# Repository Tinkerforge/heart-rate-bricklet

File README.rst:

Heart Rate Bricklet
===================

**The development of this Bricklet was stopped.**

This repository contains the firmware source code and the hardware design
files. The documentation generator configs can be found at
https://github.com/Tinkerforge/generators

Repository Content
------------------

software/:
 * examples/: Examples for all supported languages
 * build/: Compiled files
 * src/: Source code of firmware
 * Makefile: Makefile to build project

hardware/:
 * Contains KiCad project files and additionally schematics as PDF

datasheets/:
 * Contains datasheets for sensors and complex ICs that are used

Hardware
--------

The hardware is designed with the open source EDA Suite KiCad
(http://www.kicad.org). Before you are able to open the files,
you have to install the Tinkerforge kicad-libraries
(https://github.com/Tinkerforge/kicad-libraries). You can either clone
them directly in hardware/ or clone them in a separate folder and
symlink them into hardware/
(ln -s kicad_path/kicad-libraries project_path/hardware). After that you
can open the .pro file in hardware/ with KiCad and from there view and
modify the schematics and the PCB layout.

Software
--------

If you want to do your own Brick/Bricklet firmware development we highly
recommend that you use our build environment setup script and read the
tutorial (https://www.tinkerforge.com/en/doc/Tutorials/Tutorial_Build_Environment/Tutorial.html).

To compile the C code we recommend you to install the newest GNU Arm Embedded
Toolchain (https://launchpad.net/gcc-arm-embedded/+download).
You also need to install bricklib (https://github.com/Tinkerforge/bricklib)
and brickletlib (https://github.com/Tinkerforge/brickletlib).

You can either clone it directly in software/src/ or clone it in a
separate folder and symlink it into software/src/
(ln -s bricklib_path/bricklib project_path/software/src/ and
ln -s brickletlib_path/brickletlib project_path/software/src/).
Finally make sure to have CMake installed
(http://www.cmake.org/cmake/resources/software.html).

After that you can build the firmware by invoking make in software/.
The firmware (.bin) can then be found in software/build/ and uploaded
with brickv (click button "Flashing" on start screen).

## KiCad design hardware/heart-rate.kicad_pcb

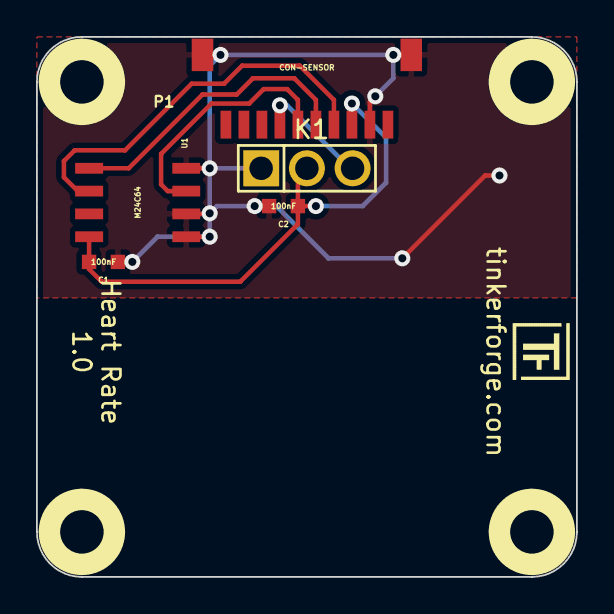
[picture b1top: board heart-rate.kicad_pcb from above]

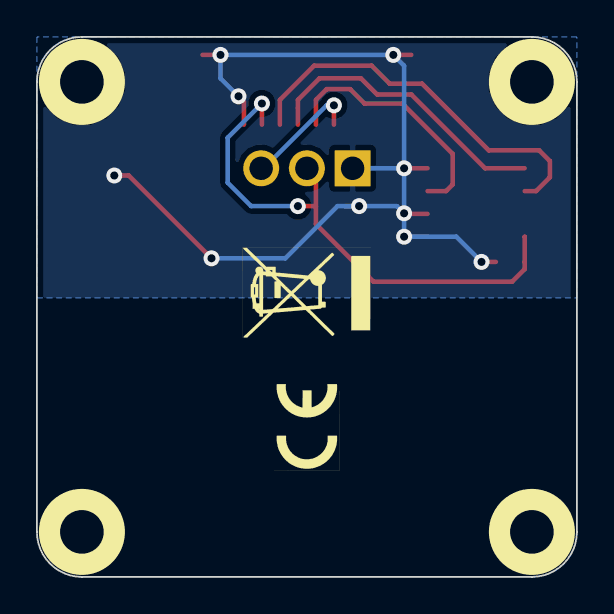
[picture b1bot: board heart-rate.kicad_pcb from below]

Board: 2 copper layers, 30.0 x 30.0 mm, 11 parts (2 on the bottom side), 6 nets.

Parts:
C1, C2: 100nF; 0603
K1: CONN_3; PIN_ARRAY_3X1
P1: CON-SENSOR
U1: M24C64; SOIC8
U2, U3, U4, U5: DRILL; DRILL_NP
VAL: CE_5mm
VAL#2: WEEE_7mm

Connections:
GND: C1.1, C2.2, K1.1, P1.2, P1.EP, U1.1, U1.2, U1.4
unnamed: K1.3, P1.7
unnamed: P1.6, U1.3
SCL: P1.4, U1.6
SDA: P1.5, U1.5
VCC: C1.2, C2.1, K1.2, P1.3, U1.8

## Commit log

2014-03-13 heart-rate-bricklet: adding firmware source
2014-03-13 heart-rate-bricklet: adding perl examples
2014-03-13 heart-rate-bricklet: adding php exmaples
2014-03-13 heart-rate-bricklet: adding java examples
2014-03-13 heart-rate-bricklet: adding C examples
2014-03-13 heart-rate-bricklet: adding javascript examples
2014-03-13 heart-rate-bricklet: adding csharp exmaples
2014-03-13 heart-rate-bricklet: adding VB.NET examples
2014-03-13 heart-rate-bricklet: adding ruby examples
2014-03-13 heart-rate-bricklet: adding delphi examples
2014-03-13 heart-rate-bricklet: adding shell examples
2014-03-19 heart rate sensor bricklet hardware files
2014-04-02 java: Unify constants style
2014-04-02 perl: Unify print style
2014-04-16 new errata
2014-07-15 java: Replace System.console() usage with an Eclipse compatible pattern
2014-08-06 Some whitespace and string cleanup
2015-02-13 csharp,vbnet: Use ReadLine instead of ReadKey
    Because ReadKey doesn't work with a pipe as stdin on the RED Brick.
2015-02-13 csharp: Use ReadLine instead of ReadKey
    Because ReadKey doesn't work with a pipe as stdin on the RED Brick.
2015-03-02 windows: Stop cmake from searching for mingw32-make.exe
    Using MinGW Makefiles as generator makes cmake search for mingw32-make.exe
    which might not be installed because GnuWin32's make.exe is used instead.
2015-04-09 c: Whitespace
2015-06-18 Break long lines in JavaScript examples
    Remove JavaScript bindings.
2015-06-24 javascript: Clean up output creation
2015-06-24 java: Remove unnecessary parentheses
2015-06-24 Fix typos in examples
2015-06-24 vbnet: Use correct type
2015-07-23 Make JavaScript browser example textarea readonly
2015-07-25 Remove double readonly
2015-07-27 Cleanup C/C++, C#, Java, Python and Ruby examples
2015-07-29 Reformat changelog
2015-08-07 Use full device class name in Python examples
2015-08-12 Fix minor warnings in C/C++ examples
2015-08-14 Cleanup Delphi examples
2015-08-18 Cleanup VB.NET examples
2015-08-19 Cleanup Perl examples
2015-08-21 Use shorter print statement in Perl example
2015-09-10 Duplicate cmake call to fix bug during cmake creation
2015-09-24 Add Mathematica and MATLAB/Octave examples
2015-09-30 Generator based example cleanup
2015-11-12 matlab: Fix callback handling for R2014a
    http://undocumentedmatlab.com/blog/matlab-callbacks-for-java-events-in-r2014a
2015-11-25 Include date and commit into changelog
2016-05-18 c: Add missing device destroy call
2016-07-01 Make the change UID comment more explicit
2017-04-13 csharp: Adapt example
2017-06-02 octave: Use javaObject instead of deprecated java_new
2017-11-30 Update examples from generator
2017-12-07 mathematica: Also generate .nb files
2018-01-26 c: Fine-tune printf format
2018-02-02 Update examples
2018-02-19 javascript: Close div tag correctly
2018-02-20 Cleanup KiCad libraries config
    Ensure LibDir=kicad-libraries and LibName1=tinkerforge.
    Remove special library.
2018-05-24 perl: Use strict in examples
2018-06-28 Fix readme
2018-07-13 Add Makefile with docker support
2018-07-13 Update directory structure and build instructions
2018-07-13 Remove obsolete generate_makefile scripts
2018-09-14 vbnet: Fix typo in comment
2018-11-06 Add rust examples
2018-11-07 rust: Accept host names for ip connection, fix naming inconsistencies
2018-11-07 rust: Rename callback receivers.
2018-12-14 Add go examples.
2018-12-18 go: Change import path.
2018-12-18 go: Change import path again.
2018-12-20 rust: Reformat examples.
2019-01-24 mqtt: Add examples.
2019-01-24 mqtt: Fix example header.
2019-01-24 mqtt: Remove executable bit in example permissions.
2019-01-24 go: Minor example fixes.
2019-01-24 mqtt: Minor example fixes.
2019-03-28 mqtt: Fix whitespace.
2019-08-22 c: Adapt to bindings changes
2019-12-02 Remove examples
2019-12-02 Mark development as stopped
2020-01-13 examples: mqtt: Remove trailing whitespace.
2021-10-25 Update KiCad link
    https://www.kicad.org/blog/2021/10/Avoid-links-to-former-kicad-domain/
2022-07-06 Add license files.

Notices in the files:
hardware/heart-rate.kicad_pcb:
Licensed under CERN OHL v.1.1
Copyright (©) 2014, B.Nordmeyer
Copyright Tinkerforge GmbH 2014.
This documentation describes Open Hardware and is licensed under the
CERN OHL v. 1.1.
